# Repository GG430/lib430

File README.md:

# lib430
Automatically exported from code.google.com/p/lib430

This is my collection of MSP430 projects, use anything you want, no warranty though :)

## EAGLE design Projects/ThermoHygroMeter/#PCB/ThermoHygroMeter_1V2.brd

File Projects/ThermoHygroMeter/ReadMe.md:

These are all the files required to program the MSP430G2553 for the Thermo/HygroMeter using I2C to communicate to HDC1080

The IDE used for this project is the free code size limited version of IAR V6.40.1 (http://www.ti.com/tool/iar-kickstart)

To program the release version of the code I use the MSP430Flasher V 1.3.3
If you have a FET connected just double click the .bat file and the code will be programmed

The JTAG connection on the board is as follows.

 PCB TOP
 
   TST RST
   
   VCC GND

MSP430Flasher Version 1.3.7: This version seems to be the last one before it changed to MSPFlasher with a newer msp430.dll
http://software-dl.ti.com/msp430/msp430_public_sw/mcu/msp430/MSP430Flasher/1_03_07_00/index_FDS.html

Version 1.3.7 of the Flasher still contains the msp430.dll version 3.5.1.1

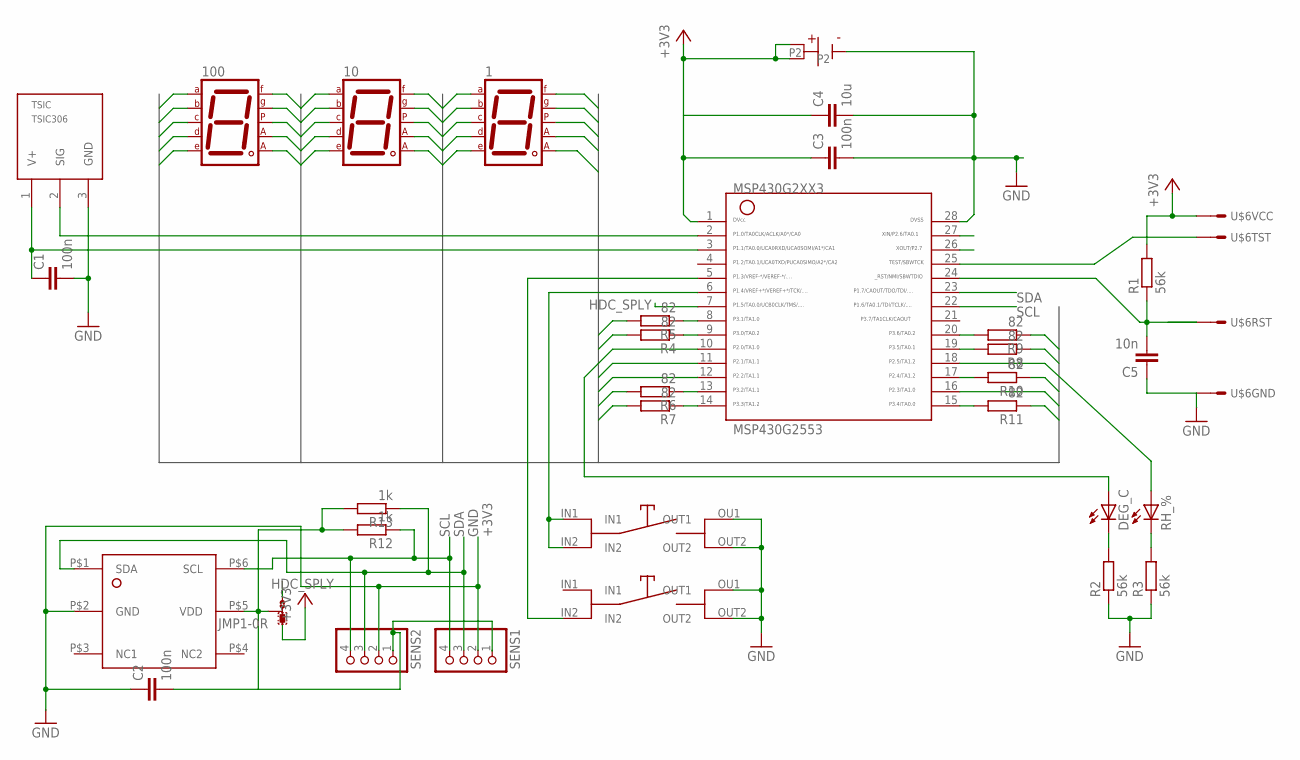
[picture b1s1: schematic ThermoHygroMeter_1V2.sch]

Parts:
1, 10, 100: 7SEG-CA; 7SEG-13
C1, C2, C3: 100n; C0805K
C4: 10u; C1808
C5: 10n; C0805K
DEG_C: LED3MM
JMP1: 0R-JUMPB; B0R-JMP
MSP430G2553: G2XX3---PW28; PW28
R1, R2, R3: 56k; R0805
R4, R5, R6, R7, R8, R9, R10, R11: 82; R0805
R12, R13: 1k; R0805
RH_%: LED3MM
SENS1, SENS2: PINHD-1X4; 1X04
SENSOR: HDKJ
TEMP/RH: HDKJ
TSIC: TSIC306; TO92-
U$1: LITHIUM320SMD; KZH20SMD
U$5: HDC1050; SON6
U$6: MSP430SBWMPE; MPE-374-04

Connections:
1: 1.3 (CA1), 1.8 (CA2), MSP430G2553.16
10: 10.3 (CA1), 10.8 (CA2), MSP430G2553.12
100: 100.3 (CA1), 100.8 (CA2), MSP430G2553.11
+3V3: C3.1, C4.1, JMP1.1, MSP430G2553.1, R1.2, U$1.P1, U$1.P2, U$6.P$1
DEG: DEG_C.A, MSP430G2553.10
GND: C1.2, C2.1, C3.2, C4.2, C5.1, MSP430G2553.28, R2.1, R3.1, SENS1.2, SENS2.2, SENSOR.OU1 (OUT1), SENSOR.OUT2, TEMP/RH.OU1 (OUT1), TEMP/RH.OUT2, TSIC.3 (GND), U$1.N, U$5.P$2 (GND), U$6.P$2
HDC_SPLY: JMP1.3, MSP430G2553.7
K1: 1.7 (A), 10.7 (A), 100.7 (A), R4.2
K2: 1.6 (B), 10.6 (B), 100.6 (B), R5.2
K3: 1.4 (C), 10.4 (C), 100.4 (C), R6.2
K4: 1.2 (D), 10.2 (D), 100.2 (D), R7.2
K5: 1.1 (E), 10.1 (E), 100.1 (E), R11.1
K6: 1.9 (F), 10.9 (F), 100.9 (F), R8.1
K7: 1.10 (G), 10.10 (G), 100.10 (G), R9.1
K8: 1.5 (DP), 10.5 (DP), 100.5 (DP), R10.1
unnamed: MSP430G2553.2, TSIC.2 (SIG)
unnamed: DEG_C.K (C), R2.2
unnamed: C1.1, MSP430G2553.3, TSIC.1 (V+)
unnamed: MSP430G2553.8, R5.1
unnamed: R3.2, RH_%.K (C)
unnamed: MSP430G2553.17, R10.2
unnamed: MSP430G2553.9, R4.1
unnamed: MSP430G2553.6, TEMP/RH.IN1, TEMP/RH.IN2
unnamed: MSP430G2553.5, SENSOR.IN2
unnamed: MSP430G2553.13, R6.1
unnamed: MSP430G2553.14, R7.1
unnamed: MSP430G2553.20, R9.2
unnamed: MSP430G2553.19, R8.2
unnamed: MSP430G2553.15, R11.2
RH: MSP430G2553.18, RH_%.A
RST: C5.2, MSP430G2553.24, R1.1, U$6.P$3
SCL: MSP430G2553.22, R12.1, SENS1.4, SENS2.4, U$5.P$6 (SCL)
SDA: MSP430G2553.23, R13.1, SENS1.3, SENS2.3, U$5.P$1 (SDA)
TST: MSP430G2553.25, U$6.P$4
V_HDC: C2.2, JMP1.2, R12.2, R13.2, SENS1.1, SENS2.1, U$5.P$5 (VDD)

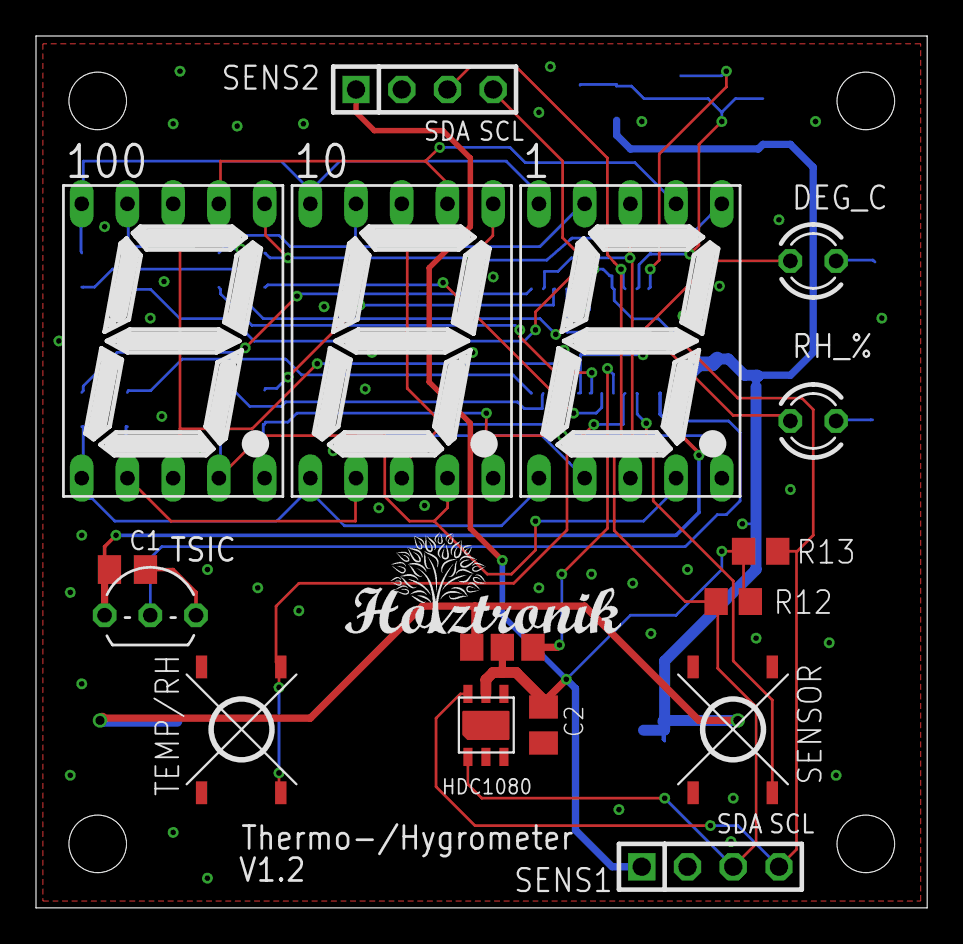
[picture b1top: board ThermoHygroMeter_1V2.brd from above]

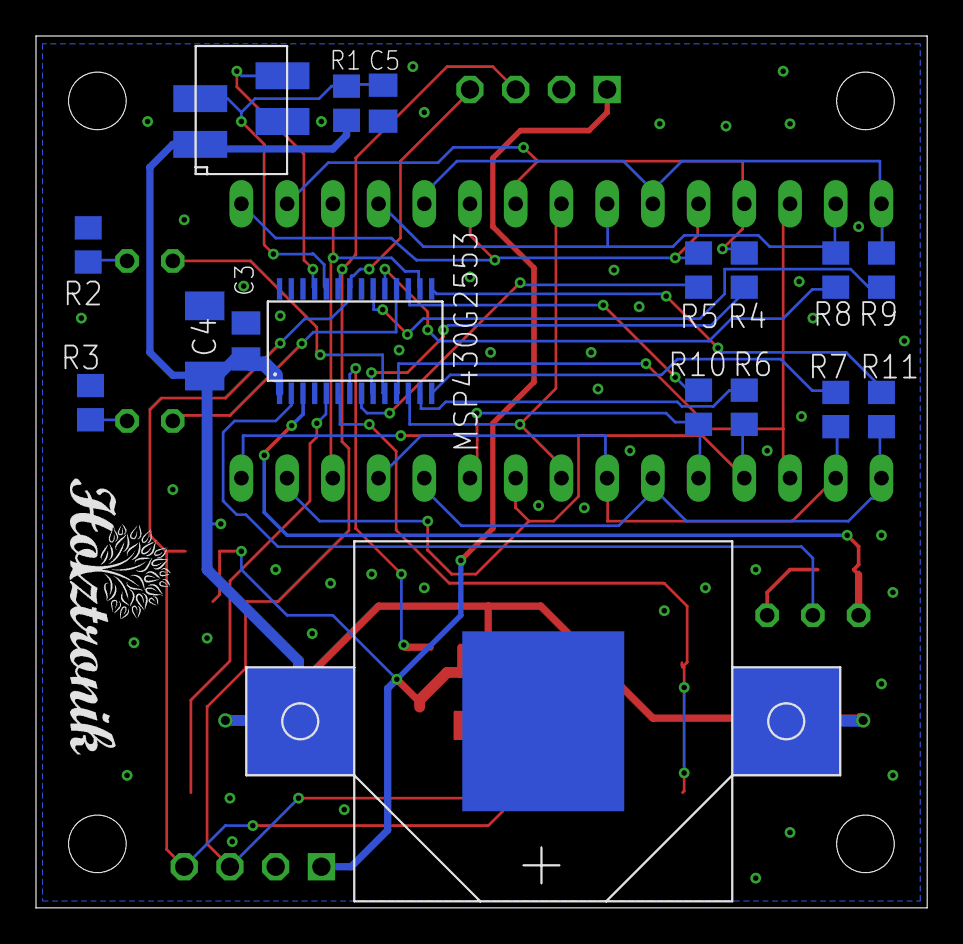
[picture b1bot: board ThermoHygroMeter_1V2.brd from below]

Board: 2 copper layers, 49.5 x 48.4 mm, 35 parts (18 on the bottom side), 35 nets.

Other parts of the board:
U$2, U$4: HOLZTRONIK4

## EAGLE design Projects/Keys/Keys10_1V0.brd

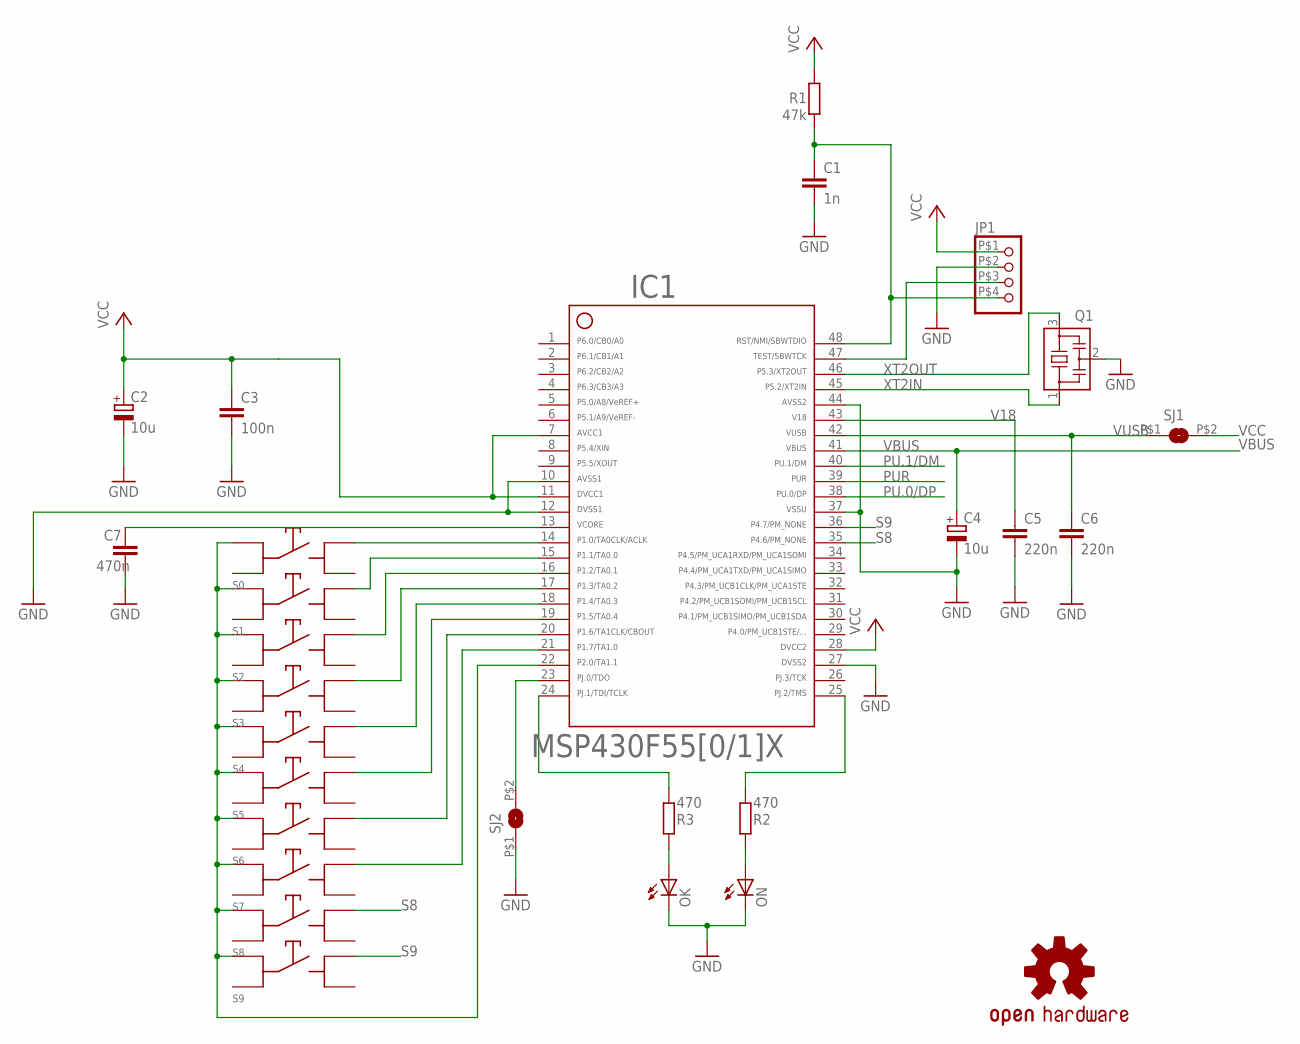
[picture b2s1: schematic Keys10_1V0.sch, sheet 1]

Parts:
C1: 1n; C0805
C2, C4: 10u; R/2012-12R
C3: 100n; C0805
C5, C6: 220n; C0805
C7: 470n; C0805
IC1: F5509; PT48
JP1: PINHD-1X4S; 1X04S
OK: LEDCHIPLED_0805; CHIPLED_0805
ON: LEDCHIPLED_0805; CHIPLED_0805
Q1: PIEZO_CSTCR4M00G15L99; CSTCR6M
R1: 47k; R0805
R2, R3: 470; R0805
S0, S1, S2, S3, S4, S5, S6, S7, S8, S9: HDKJ
SJ1, SJ2: SJM; SJ_M
U$1: OSHW_LOGO_SYMS; OSHW_LOGO_SMALL_SYM

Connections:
GND: C1.2, C2.-, C3.2, C4.-, C5.2, C6.2, C7.2, IC1.10, IC1.12, IC1.27, IC1.37, IC1.44, JP1.P$2 (2), OK.C, ON.C, Q1.2, SJ2.P$1 (1); also elsewhere on the board
LED1: ON.A, R2.2
LED_OK: IC1.24, R3.1
LED_ON: IC1.25, R2.1
unnamed: IC1.23, SJ2.P$2 (2)
unnamed: OK.A, R3.2
PU.0/DP: IC1.38; also elsewhere on the board
PU.1/DM: IC1.40; also elsewhere on the board
PUR: IC1.39; also elsewhere on the board
RST: C1.1, IC1.48, JP1.P$4 (4), R1.1
S0: IC1.14, S0.OU1 (OUT1)
S1: IC1.15, S1.OU1 (OUT1)
S2: IC1.16, S2.OU1 (OUT1)
S3: IC1.17, S3.OU1 (OUT1)
S4: IC1.18, S4.OU1 (OUT1)
S5: IC1.19, S5.OU1 (OUT1)
S6: IC1.20, S6.OU1 (OUT1)
S7: IC1.21, S7.OU1 (OUT1)
S8: IC1.35, S8.OU1 (OUT1)
S9: IC1.36, S9.OU1 (OUT1)
SC: IC1.22, S0.IN1, S1.IN1, S2.IN1, S3.IN1, S4.IN1, S5.IN1, S6.IN1, S7.IN1, S8.IN1, S9.IN1
TST: IC1.47, JP1.P$3 (3)
V18: C5.1, IC1.43
VBUS: C4.+, IC1.41; also elsewhere on the board
VCC: C2.+, C3.1, IC1.7, IC1.11, IC1.28, JP1.P$1 (1), R1.2, SJ1.P$2 (2); also elsewhere on the board
VCORE: C7.1, IC1.13
VUSB: C6.1, IC1.42, SJ1.P$1 (1)
XT2IN: IC1.45, Q1.1
XT2OUT: IC1.46, Q1.3

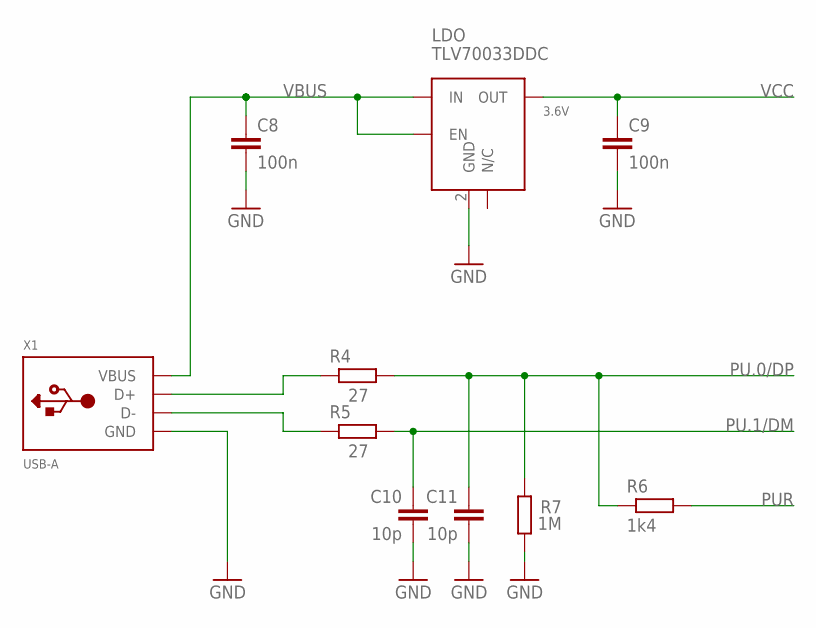
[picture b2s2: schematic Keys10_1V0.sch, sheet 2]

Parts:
C8, C9: 100n; C0805
C10, C11: 10p; C0805
LDO: TLV70033DDC; SOT23-5
R4, R5: 27; R0805
R6: 1k4; R0805
R7: 1M; R0805
X1: USB-A; MOLEX_480371000

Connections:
EZFET_DM: R5.1, X1.2 (D-)
EZFET_DP: R4.1, X1.3 (D+)
GND: C8.2, C9.2, C10.2, C11.2, LDO.2 (GND), R7.2, X1.4 (GND), X1.M1 (GND), X1.M2 (GND); also elsewhere on the board
PU.0/DP: C11.1, R4.2, R6.1, R7.1; also elsewhere on the board
PU.1/DM: C10.1, R5.2; also elsewhere on the board
PUR: R6.2; also elsewhere on the board
VBUS: C8.1, LDO.1 (IN), LDO.3 (EN), X1.1 (VBUS); also elsewhere on the board
VCC: C9.1, LDO.5 (OUT); also elsewhere on the board

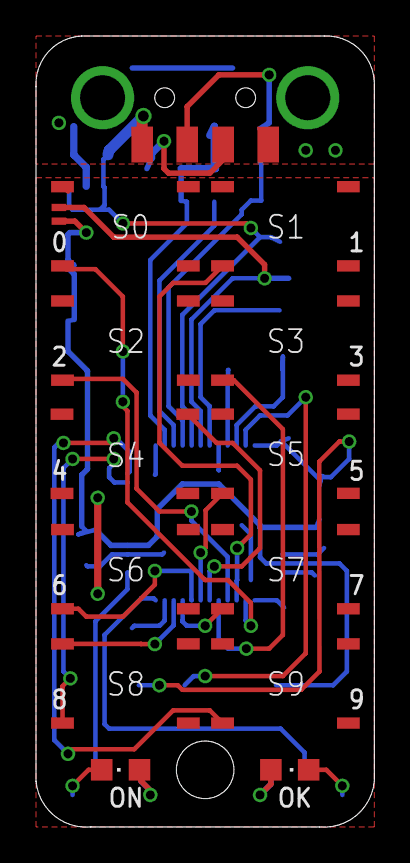
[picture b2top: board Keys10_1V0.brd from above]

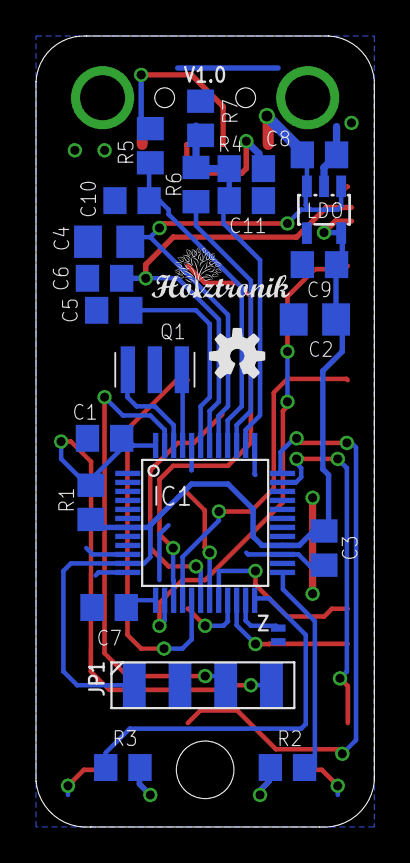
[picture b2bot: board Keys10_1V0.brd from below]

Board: 2 copper layers, 18.8 x 44.0 mm, 39 parts (25 on the bottom side), 31 nets.

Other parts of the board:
U$3: HOLZTRONIK3

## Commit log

2016-03-13 7 Segment Uhr V1.0.2 from SVN export
2016-05-31 Add files via upload
    V1.2.2
2016-05-31 Add files via upload
    New version of charlieplexing
2016-05-31 Photos added
2016-05-31 Sonnenuhr V1.2.2 in CCS added
2016-08-11 Keys 1V0
2016-10-15 New Project ThermoHygroMeter created
2016-10-15 txt to view updated
2016-10-15 Initial File Upload
2016-10-15 Updated ThermoHygroMeter with full project files
2016-10-15 Version of Flasher set to V1.3.7
2016-10-15 readme updated with Flasher info
2016-10-15 IAR Download added
2016-10-15 Thermo-/Hygrometer PCBs added

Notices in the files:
parts and their libraries:
PatternAgents-Logos: License : http://creativecommons.org/licenses/by-sa/3.0
(Creative Commons 3.0)
